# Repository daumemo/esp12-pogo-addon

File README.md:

# esp12-pogo-addon

Addon with pogo pins for ESP-12 flashing.

More information: https://daumemo.com/pogo-addon-for-esp-module-programming/

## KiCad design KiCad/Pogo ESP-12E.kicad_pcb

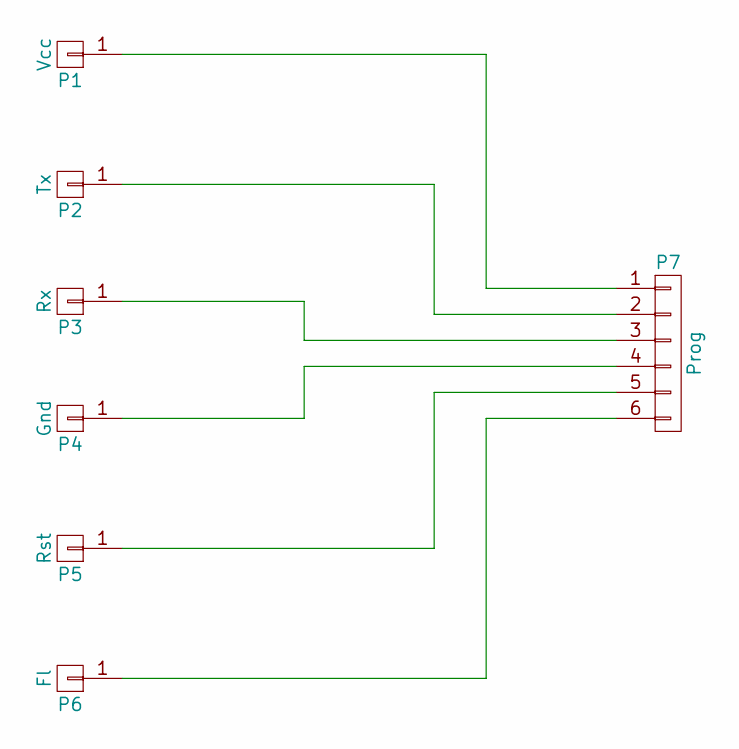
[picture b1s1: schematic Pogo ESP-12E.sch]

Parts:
P1: Vcc; Pin_Header_Straight_1x01
P2: Tx; Pin_Header_Straight_1x01
P3: Rx; Pin_Header_Straight_1x01
P4: Gnd; Pin_Header_Straight_1x01
P5: Rst; Pin_Header_Straight_1x01
P6: Fl; Pin_Header_Straight_1x01
P7: Prog; Pin_Header_Straight_1x06

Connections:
unnamed: P1.1, P7.1
unnamed: P2.1, P7.2
unnamed: P3.1, P7.3
unnamed: P4.1, P7.4
unnamed: P5.1, P7.5
unnamed: P6.1, P7.6

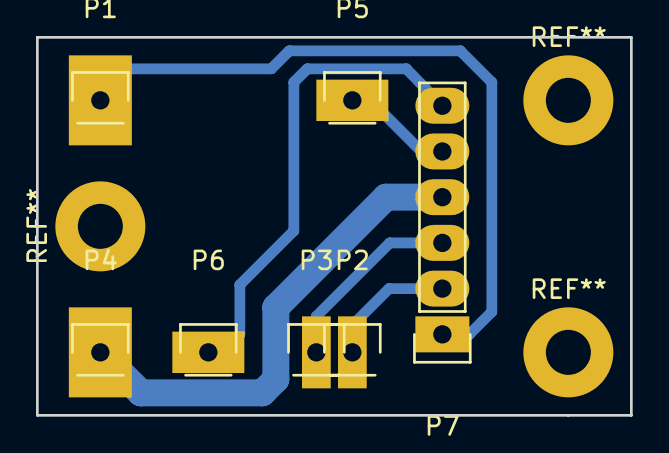
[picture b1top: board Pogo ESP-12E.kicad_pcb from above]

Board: 2 copper layers, 33.0 x 21.0 mm, 7 parts (0 on the bottom side), 6 nets.
